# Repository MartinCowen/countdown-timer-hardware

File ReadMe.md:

# Child-friendly Countdown Timer  
Electronic PCB and Front Panel to fit Hammond RL6655, designed in Kicad 9.0

## Main components
 - STM32C031C6: Cortex-M0+, 32kB flash, 12kB RAM, 45 IOs
 - 0.8 inch 7-segment displays SA08-11SURKWA
 - C&K D6 buttons
 - USB micro powered from a battery pack, 0.6mA in sleep.

## PCB parameters
Two layers, mix of surface mount and through hole components, ground plane fill.

## Bill of Materials
SMT Part numbers for LCSC (JLC) 
Through hole, SMTs not available at LCSC and mechanical parts from RS or Mouser.

## Front Panel
PCB with black solder mask, white silkscreen, cutouts for displays, LEDs, buttons, mounting holes. Replaces front panel on RL6655, main PCB is mounted behind it.

## Additional components needed
 - Either a 5V 0.5A PSU (phone charger) or portable battery with USB output
 - USB A to USB micro short cable for the portable battery
 - Cable ties to hold battery back to back of PCB
 - optional: Display filter material, 40x100mm, < 1mm thick.
 - for programming: STLINK-V3MINIE with ribbon cable from [STM32C0316-DK](https://www.st.com/en/evaluation-tools/stm32c0316-dk.html)
 - for programming: USB C cable to your laptop (USB C or USB A) from the STLINK

## Firmware
[Firmware in C for STM32C031C6](https://github.com/MartinCowen/countdown-timer-firmware) built in STM32CubeIDE

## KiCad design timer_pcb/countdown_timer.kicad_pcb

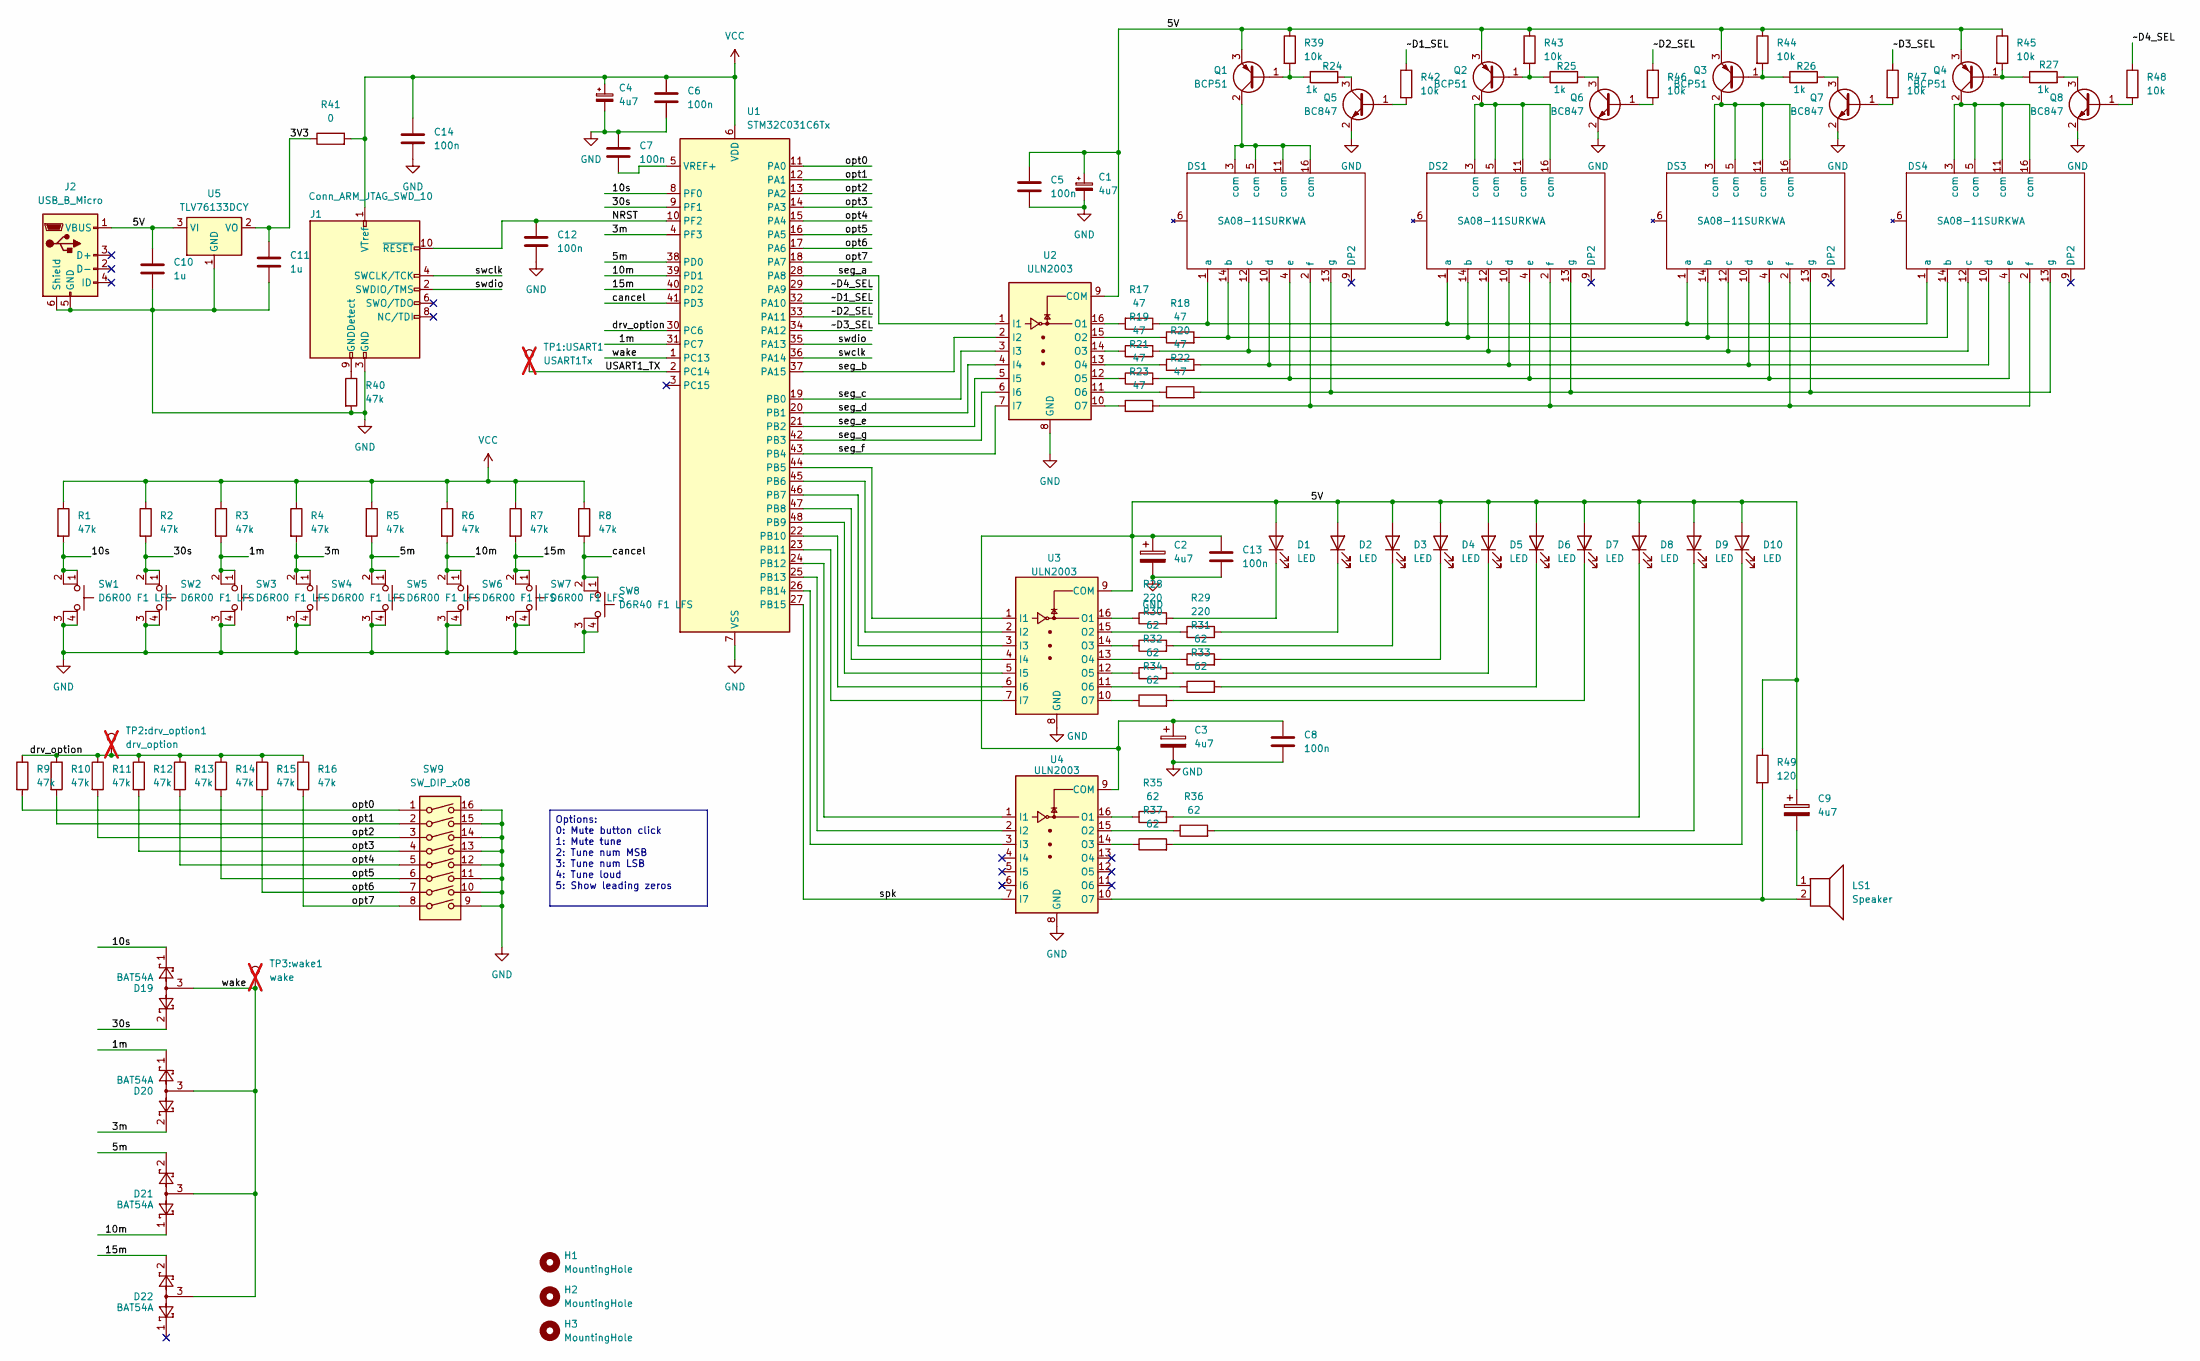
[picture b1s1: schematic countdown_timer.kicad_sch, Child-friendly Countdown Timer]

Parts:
C1, C2, C3, C4, C9: 4u7; CP_Elec_4x5.4; LCSC C59949
C5, C6, C7, C8, C12, C13, C14: 100n; C_0805_2012Metric; LCSC C49678
C10, C11: 1u; C_0805_2012Metric; LCSC C24123
D1, D2, D3, D4, D5, D6, D7, D8, D9, D10: LED; LED_D5.0mm_FlatTop; LCSC DNP
D19, D20, D21, D22: BAT54A; SOT-323_SC-70; LCSC C77317
DS1, DS2, DS3, DS4: SA08-11SURKWA; LCSC DNP
H1, H2, H3: MountingHole; ToolingHole_1.152mm; LCSC DNP
J1: Conn_ARM_JTAG_SWD_10; PinHeader_2x05_P1.27mm_Vertical_SMD; LCSC C5155080
J2: USB_B_Micro; USB_Micro-B_Amphenol_10118194-0001LF_Horizontal; LCSC C132563
LS1: Speaker; CMS-151504-SMT-TR; LCSC DNP
Q1, Q2, Q3, Q4: BCP51; SOT-223-3_TabPin2; LCSC C41375111
Q5, Q6, Q7, Q8: BC847; SOT-323_SC-70; LCSC C8659
R1, R2, R3, R4, R5, R6, R7, R8, R9, R10, R11, R12, R13, R14, R15, R16, R40: 47k; R_0805_2012Metric; LCSC C17713
R17, R18, R19, R20, R21, R22, R23: 47; R_0805_2012Metric; LCSC C17714
R24, R25, R26, R27: 1k; R_0805_2012Metric; LCSC C17513
R28, R29: 220; R_0805_2012Metric; LCSC C17557
R30, R31, R32, R33, R34, R35, R36, R37: 62; R_0805_2012Metric; LCSC C17557
R39, R42, R43, R44, R45, R46, R47, R48: 10k; R_0805_2012Metric; LCSC C17414
R41: 0; R_0805_2012Metric; LCSC C17477
R49: 120; R_0805_2012Metric; LCSC C17437
SW1, SW2, SW3, SW4, SW5, SW6, SW7: D6R00 F1 LFS; CK_D6; LCSC C221608
SW8: D6R40 F1 LFS; CK_D6; LCSC C668538
SW9: SW_DIP_x08; DIP-16_W7.62mm; LCSC C108707
TP1:USART1: USART1Tx; TestPoint_Pad_D1.5mm; LCSC DNP; not fitted
TP2:drv_option1: drv_option; TestPoint_Pad_D1.5mm; LCSC DNP; not fitted
TP3:wake1: wake; TestPoint_Pad_D1.5mm; LCSC DNP; not fitted
U1: STM32C031C6Tx; LQFP-48_7x7mm_P0.5mm; LCSC C5456218
U2, U3, U4: ULN2003; SOIC-16_3.9x9.9mm_P1.27mm; LCSC C7512
U5: TLV76133DCY; SOT-223-3_TabPin2; LCSC C7527500

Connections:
/1m: D20.1, R3.2, SW3.1, SW3.2, U1.31 (PC7)
/3V3: C11.1, R41.1, U5.2 (VO)
/3m: D20.2, R4.2, SW4.1, SW4.2, U1.4 (PF3)
/5V: C1.1, C2.1, C3.1, C5.1, C8.1, C9.1, C10.1, C13.1, D1.2 (A), D2.2 (A), D3.2 (A), D4.2 (A), D5.2 (A), D6.2 (A), D7.2 (A), D8.2 (A), D9.2 (A), D10.2 (A), J2.1 (VBUS), Q1.3 (E), Q2.3 (E), Q3.3 (E), Q4.3 (E), R39.1, R43.1, R44.1, R45.1, R49.1, U2.9 (COM), U3.9 (COM), U4.9 (COM), U5.3 (VI)
/5m: D21.2, R5.2, SW5.1, SW5.2, U1.38 (PD0)
/10m: D21.1, R6.2, SW6.1, SW6.2, U1.39 (PD1)
/10s: D19.1, R1.2, SW1.1, SW1.2, U1.8 (PF0)
/15m: D22.2, R7.2, SW7.1, SW7.2, U1.40 (PD2)
/30s: D19.2, R2.2, SW2.1, SW2.2, U1.9 (PF1)
/NRST: C12.1, J1.10 (~RESET), U1.10 (PF2)
/USART1_TX: TP1:USART1.1, U1.2 (PC14)
/cancel: R8.2, SW8.1, SW8.2, U1.41 (PD3)
/drv_option: R9.1, R10.1, R11.1, R12.1, R13.1, R14.1, R15.1, R16.1, TP2:drv_option1.1, U1.30 (PC6)
/opt0: R9.2, SW9.1, U1.11 (PA0)
/opt1: R10.2, SW9.2, U1.12 (PA1)
/opt2: R11.2, SW9.3, U1.13 (PA2)
/opt3: R12.2, SW9.4, U1.14 (PA3)
/opt4: R13.2, SW9.5, U1.15 (PA4)
/opt5: R14.2, SW9.6, U1.16 (PA5)
/opt6: R15.2, SW9.7, U1.17 (PA6)
/opt7: R16.2, SW9.8, U1.18 (PA7)
/seg_a: U1.28 (PA8), U2.1 (I1)
/seg_b: U1.37 (PA15), U2.2 (I2)
/seg_c: U1.19 (PB0), U2.3 (I3)
/seg_d: U1.20 (PB1), U2.4 (I4)
/seg_e: U1.21 (PB2), U2.5 (I5)
/seg_f: U1.43 (PB4), U2.7 (I7)
/seg_g: U1.42 (PB3), U2.6 (I6)
/spk: U1.27 (PB15), U4.7 (I7)
/swclk: J1.4 (SWCLK/TCK), U1.36 (PA14)
/swdio: J1.2 (SWDIO/TMS), U1.35 (PA13)
/wake: D19.3, D20.3, D21.3, D22.3, TP3:wake1.1, U1.1 (PC13)
/~D1_SEL: R42.1, U1.32 (PA10)
/~D2_SEL: R46.1, U1.33 (PA11)
/~D3_SEL: R47.1, U1.34 (PA12)
/~D4_SEL: R48.1, U1.29 (PA9)
GND: C1.2, C2.2, C3.2, C4.2, C5.2, C6.2, C7.1, C8.2, C10.2, C11.2, C12.2, C13.2, C14.2, J1.3 (GND), J1.5 (GND), J2.5 (GND), J2.6 (Shield), Q5.2 (E), Q6.2 (E), Q7.2 (E), Q8.2 (E), R40.2, SW1.3 (K), SW1.4 (A), SW2.3 (K), SW2.4 (A), SW3.3 (K), SW3.4 (A), SW4.3 (K), SW4.4 (A), SW5.3 (K), SW5.4 (A), SW6.3 (K), SW6.4 (A), SW7.3 (K), SW7.4 (A), SW8.3 (K), SW8.4 (A), SW9.9, SW9.10, SW9.11, SW9.12, SW9.13, SW9.14, SW9.15, SW9.16, U1.7 (VSS), U2.8 (GND), U3.8 (GND), U4.8 (GND), U5.1 (GND)
unnamed: C9.2, LS1.1
unnamed: D1.1 (K), R28.2
unnamed: D2.1 (K), R29.2
unnamed: D3.1 (K), R30.2
unnamed: D4.1 (K), R31.2
unnamed: D5.1 (K), R32.2
unnamed: D6.1 (K), R33.2
unnamed: D7.1 (K), R34.2
unnamed: D8.1 (K), R35.2
unnamed: D9.1 (K), R36.2
unnamed: D10.1 (K), R37.2
unnamed: DS1.1 (a), DS2.1 (a), DS3.1 (a), DS4.1 (a), R17.1
unnamed: DS1.14 (b), DS2.14 (b), DS3.14 (b), DS4.14 (b), R18.2
unnamed: DS1.12 (c), DS2.12 (c), DS3.12 (c), DS4.12 (c), R19.2
unnamed: DS1.10 (d), DS2.10 (d), DS3.10 (d), DS4.10 (d), R20.2
unnamed: DS1.4 (e), DS2.4 (e), DS3.4 (e), DS4.4 (e), R21.2
unnamed: DS1.2 (f), DS2.2 (f), DS3.2 (f), DS4.2 (f), R23.2
unnamed: DS1.13 (g), DS2.13 (g), DS3.13 (g), DS4.13 (g), R22.2
unnamed: J1.9 (GNDDetect), R40.1
unnamed: Q1.1 (B), R24.1, R39.2
unnamed: DS1.3 (com), DS1.5 (com), DS1.11 (com), DS1.16 (com), Q1.2 (C)
unnamed: Q2.1 (B), R25.1, R43.2
unnamed: DS2.3 (com), DS2.5 (com), DS2.11 (com), DS2.16 (com), Q2.2 (C)
unnamed: Q3.1 (B), R26.1, R44.2
unnamed: DS3.3 (com), DS3.5 (com), DS3.11 (com), DS3.16 (com), Q3.2 (C)
unnamed: Q4.1 (B), R27.1, R45.2
unnamed: DS4.3 (com), DS4.5 (com), DS4.11 (com), DS4.16 (com), Q4.2 (C)
unnamed: Q5.1 (B), R42.2
unnamed: Q5.3 (C), R24.2
unnamed: Q6.1 (B), R46.2
unnamed: Q6.3 (C), R25.2
unnamed: Q7.1 (B), R47.2
unnamed: Q7.3 (C), R26.2
unnamed: Q8.1 (B), R48.2
unnamed: Q8.3 (C), R27.2
unnamed: U1.44 (PB5), U3.1 (I1)
unnamed: U1.45 (PB6), U3.2 (I2)
unnamed: U1.46 (PB7), U3.3 (I3)
unnamed: U1.47 (PB8), U3.4 (I4)
unnamed: U1.48 (PB9), U3.5 (I5)
unnamed: U1.22 (PB10), U3.6 (I6)
unnamed: U1.23 (PB11), U3.7 (I7)
unnamed: U1.24 (PB12), U4.1 (I1)
unnamed: U1.25 (PB13), U4.2 (I2)
unnamed: U1.26 (PB14), U4.3 (I3)
unnamed: C7.2, U1.5 (VREF+)
unnamed: R17.2, U2.16 (O1)
unnamed: R18.1, U2.15 (O2)
unnamed: R19.1, U2.14 (O3)
unnamed: R20.1, U2.13 (O4)
unnamed: R21.1, U2.12 (O5)
unnamed: R22.1, U2.11 (O6)
unnamed: R23.1, U2.10 (O7)
unnamed: R28.1, U3.16 (O1)
unnamed: R29.1, U3.15 (O2)
unnamed: R30.1, U3.14 (O3)
unnamed: R31.1, U3.13 (O4)
unnamed: R32.1, U3.12 (O5)
unnamed: R33.1, U3.11 (O6)
unnamed: R34.1, U3.10 (O7)
unnamed: R35.1, U4.16 (O1)
unnamed: R36.1, U4.15 (O2)
unnamed: R37.1, U4.14 (O3)
unnamed: LS1.2, R49.2, U4.10 (O7)
VCC: C4.1, C6.1, C14.1, J1.1 (VTref), R1.1, R2.1, R3.1, R4.1, R5.1, R6.1, R7.1, R8.1, R41.2, U1.6 (VDD)

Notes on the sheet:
Options: 0: Mute button click 1: Mute tune 2: Tune num MSB 3: Tune num LSB 4: Tune loud 5: Show leading zeros

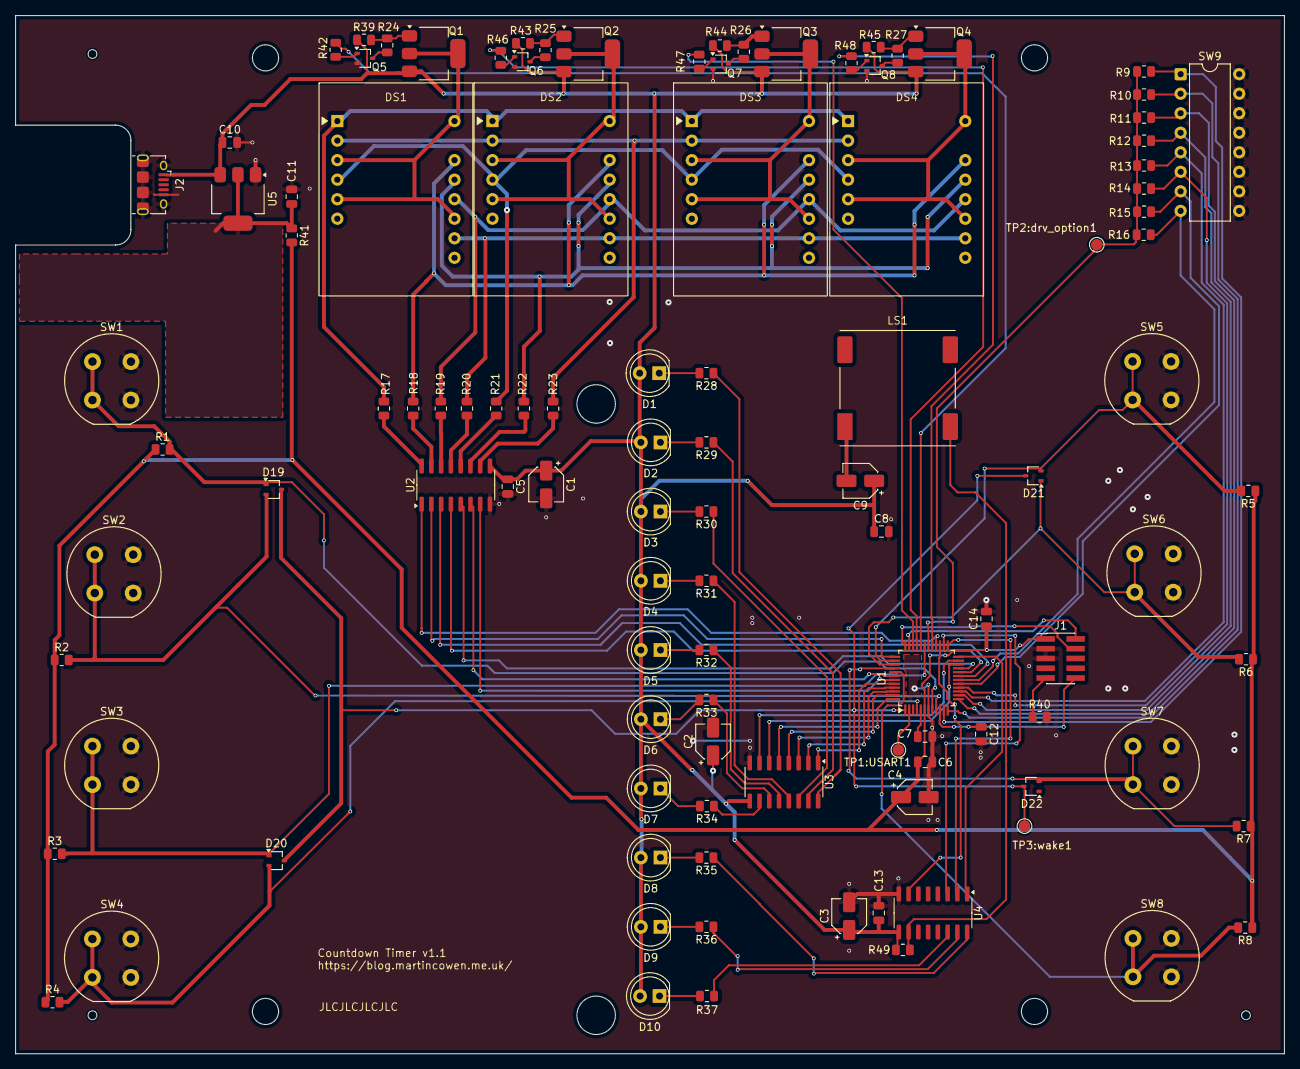
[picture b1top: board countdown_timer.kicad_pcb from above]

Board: 2 copper layers, 164.9 x 134.9 mm, 111 parts (0 on the bottom side), 102 nets.

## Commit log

2025-09-30 Ignore backup folders anywhere in project
2025-09-30 PCB and Front Panel for version 1.1
    Incorporates corrections found with 1.0
    - seg_A now on PA8 to fix clash with a SWD pin
    - D6 button orientation
    - speaker drive circuit fixed
    - resistor values for bargraph LEDs for even brightness
    - resistor values for segment driver for improved transistor drive
2025-10-31 Added firmware repo link
